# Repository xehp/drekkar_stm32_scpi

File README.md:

# drekkar_stm32_scpi
An SCPI adapter. This code is used for setting up and reading voltage (or current) from an SCPI compatible multi meter.
It should work on a pretty much any nucleo device. Some reconfiguring regarding which serial ports to use may be needed.

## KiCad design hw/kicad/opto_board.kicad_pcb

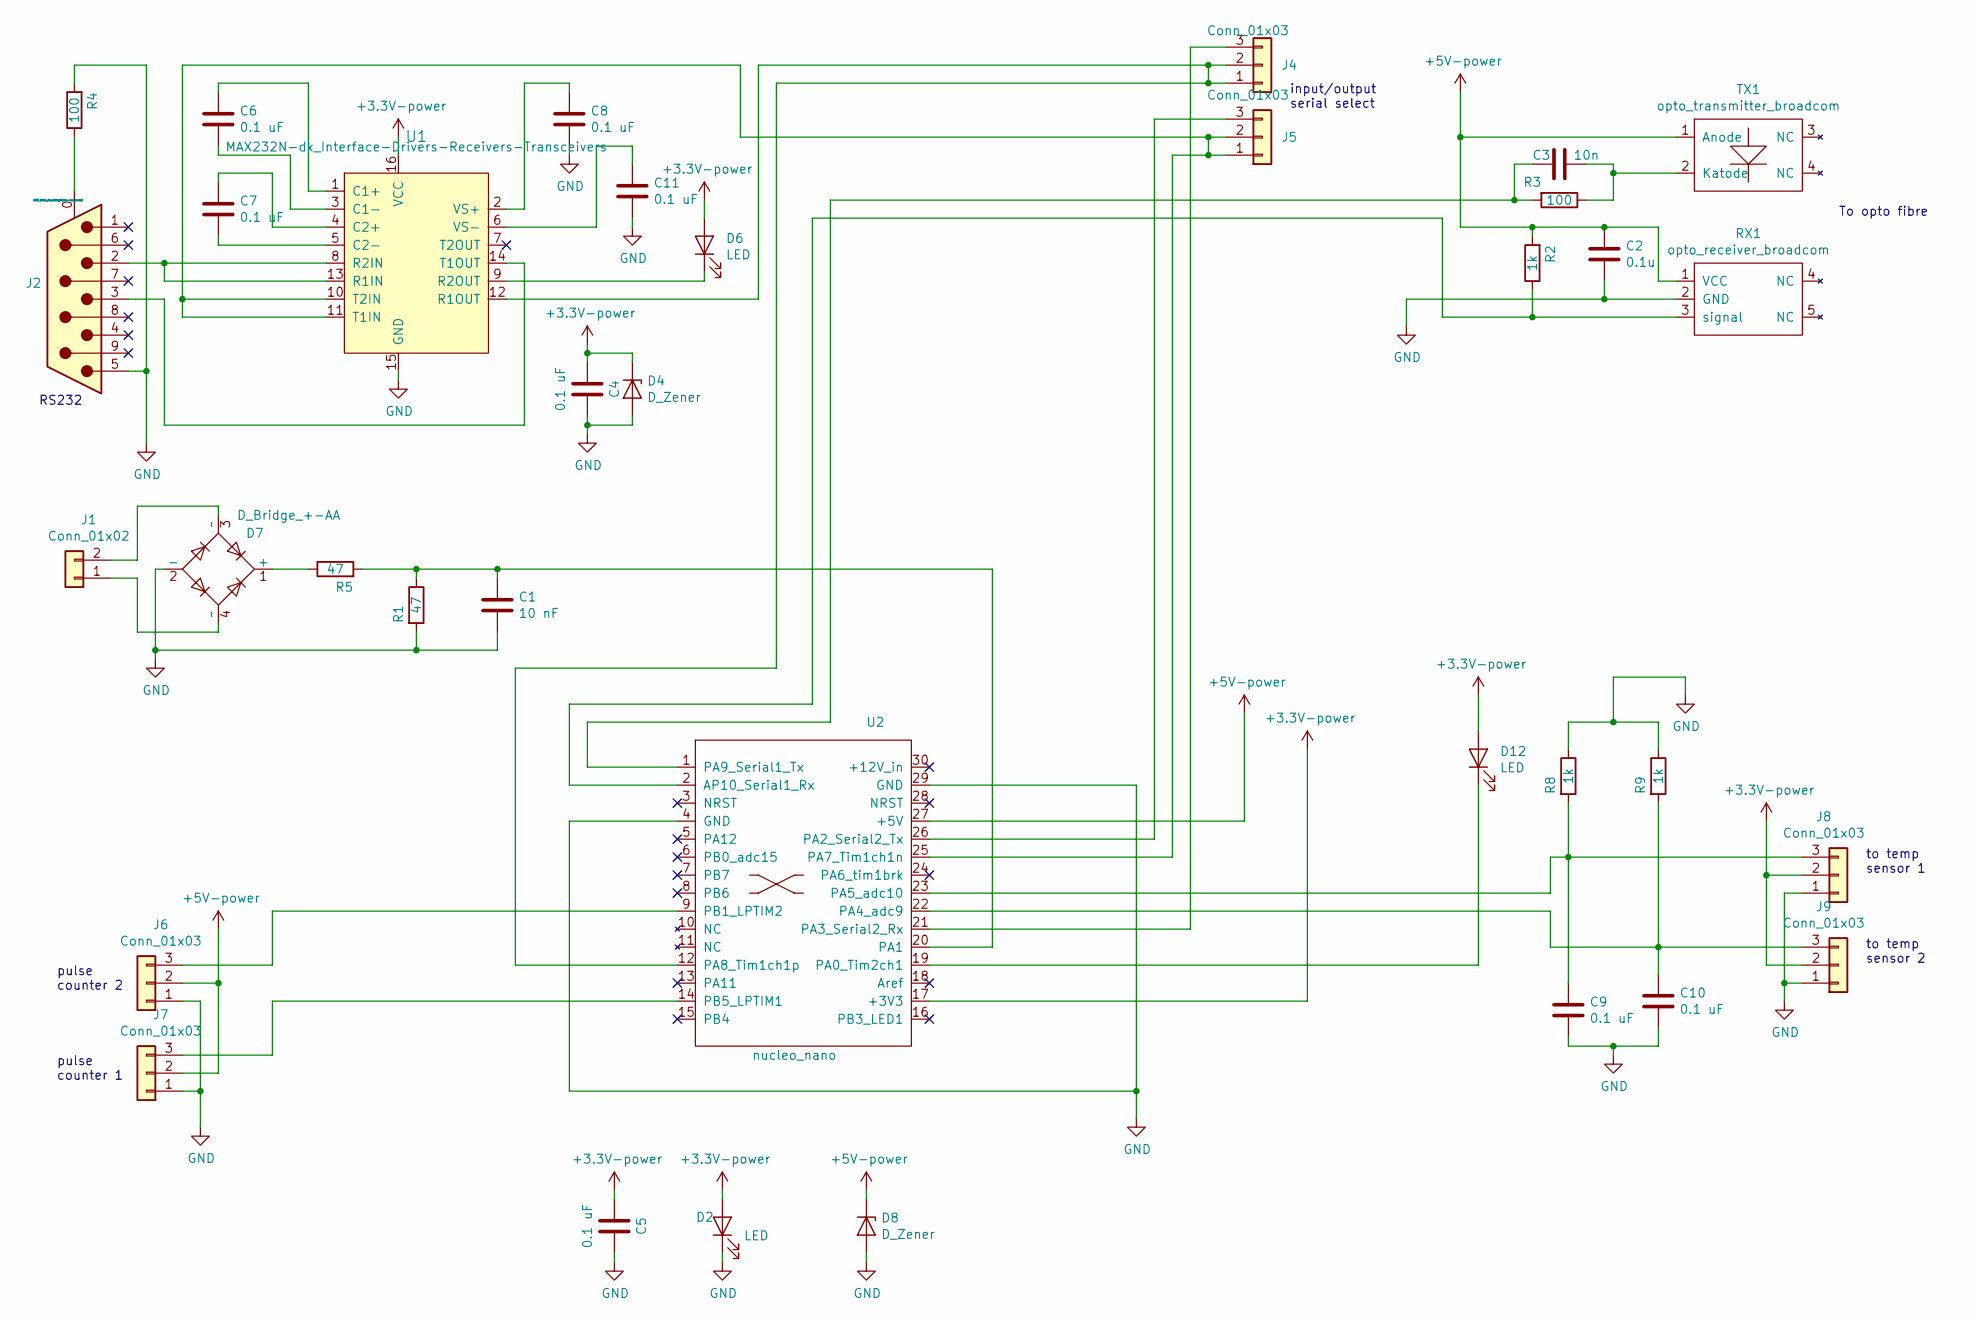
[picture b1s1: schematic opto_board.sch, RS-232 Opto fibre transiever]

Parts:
C1: 10 nF; C_Disc_D3.8mm_W2.6mm_P2.50mm
C2: 0.1u; C_Disc_D3.8mm_W2.6mm_P2.50mm
C3: 10n; C_Disc_D3.8mm_W2.6mm_P2.50mm
C4, C5, C6, C7, C8, C9, C10, C11: 0.1 uF; C_Disc_D3.8mm_W2.6mm_P2.50mm
D2, D6, D12: LED; LED_D3.0mm
D4, D8: D_Zener; D_DO-41_SOD81_P3.81mm_Vertical_AnodeUp
D7: D_Bridge_+-AA; Diode_Bridge_DIP-4_W7.62mm_P5.08mm
J1: Conn_01x02; Molex_KK-254_AE-6410-02A_1x02_P2.54mm_Vertical
J2: DB9_Male_MountingHoles-Connector; DSUB-9_Male_Horizontal_P2.77x2.84mm_EdgePinOffset7.70mm_Hou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
J4, J5: Conn_01x03; PinHeader_1x03_P2.54mm_Vertical
J6, J7, J8, J9: Conn_01x03; Molex_KK-254_AE-6410-03A_1x03_P2.54mm_Vertical
R1, R5: 47; R_Axial_DIN0309_L9.0mm_D3.2mm_P2.54mm_Vertical
R2, R8, R9: 1k; R_Axial_DIN0207_L6.3mm_D2.5mm_P2.54mm_Vertical
R3, R4: 100; R_Axial_DIN0207_L6.3mm_D2.5mm_P2.54mm_Vertical
RX1: opto_receiver_broadcom; opto_receiver_broadwell
TX1: opto_transmitter_broadcom; opto_transmitter_broadwell
U1: MAX232N-dk_Interface-Drivers-Receivers-Transceive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; DIP-16_W7.62mm; MPN MAX232N; Digi-Key_PN 296-1402-5-ND
U2: nucleo_nano

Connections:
+3V3: C4.2, C5.2, D2.2 (A), D4.1 (K), D6.2 (A), D12.2 (A), J8.2, J9.2, U1.16 (VCC), U2.17 (+3V3)
+5V: C2.2, D8.1 (K), J6.2, J7.2, R2.2, RX1.1 (VCC), TX1.1 (Anode), U2.27 (+5V)
GND: C1.1, C2.1, C4.1, C5.1, C8.1, C9.1, C10.1, C11.1, D2.1 (K), D4.2 (A), D7.2 (-), D8.2 (A), J2.5, J6.1, J7.1, J8.1, J9.1, R1.2, R4.2, R8.1, R9.1, RX1.2 (GND), U1.15 (GND), U2.4 (GND), U2.29 (GND)
unnamed: C1.2, R1.1, R5.2, U2.20 (PA1)
unnamed: C3.1, R3.1, TX1.2 (Katode)
unnamed: C3.2, R3.2, U2.1 (PA9_Serial1_Tx)
unnamed: C6.1, U1.3 (C1-)
unnamed: C6.2, U1.1 (C1+)
unnamed: C7.1, U1.5 (C2-)
unnamed: C7.2, U1.4 (C2+)
unnamed: C8.2, U1.2 (VS+)
unnamed: C9.2, J8.3, R8.2, U2.23 (PA5_adc10)
unnamed: C10.2, J9.3, R9.2, U2.22 (PA4_adc9)
unnamed: C11.2, U1.6 (VS-)
unnamed: D6.1 (K), U1.9 (R2OUT)
unnamed: D7.1 (+), R5.1
unnamed: D7.3 (~~), J1.2
unnamed: D7.4 (~~), J1.1
unnamed: D12.1 (K), U2.19 (PA0_Tim2ch1)
unnamed: J2.0 (PAD), R4.1
unnamed: J2.2, U1.8 (R2IN), U1.13 (R1IN)
unnamed: J2.3, U1.14 (T1OUT)
unnamed: J4.1, J4.2, U1.12 (R1OUT), U2.12 (PA8_Tim1ch1p)
unnamed: J4.3, U2.21 (PA3_Serial2_Rx)
unnamed: J5.1, J5.2, U1.10 (T2IN), U1.11 (T1IN), U2.25 (PA7_Tim1ch1n)
unnamed: J5.3, U2.26 (PA2_Serial2_Tx)
unnamed: J6.3, U2.9 (PB1_LPTIM2)
unnamed: J7.3, U2.14 (PB5_LPTIM1)
unnamed: R2.1, RX1.3 (signal), U2.2 (AP10_Serial1_Rx)

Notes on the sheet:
to temp sensor 1
to temp sensor 2
pulse counter 1
pulse counter 2
input/output serial select
RS232
To opto fibre

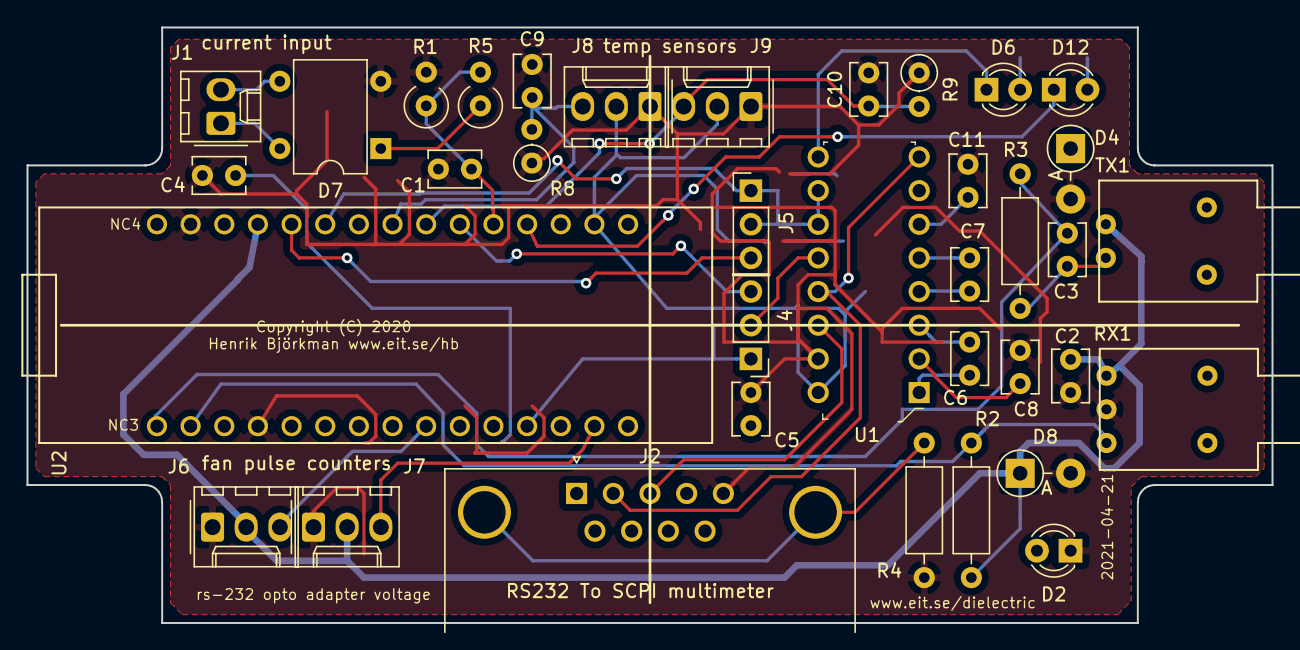
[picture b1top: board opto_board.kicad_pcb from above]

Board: 2 copper layers, 94.0 x 45.0 mm, 36 parts (0 on the bottom side), 29 nets.

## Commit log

2021-03-24 first release version
2021-03-24 removed an empty file
2021-04-09 cleanup (not tested)
2021-04-11 More cleanup (it compiles fine but is not tested)
2021-04-18 code cleanup
2021-04-21 Added HW schematics
2021-04-21 added eit_kicad_libraries
2021-04-21 updated gerber files
2021-04-21 Moved software to new folder sw
2021-04-21 moved a readme file also
2021-04-21 moved kicad files to their own folder
2021-05-13 cleanup
2021-09-06 major cleanup
2021-09-27 improved SW/HW, added bom.txt & readme.pdf

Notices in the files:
hw/kicad/opto_board.kicad_pcb:
Copyright (C) 2020
hw/kicad/opto_board.sch:
Copuright (C) 2020 Henrik Björkman
